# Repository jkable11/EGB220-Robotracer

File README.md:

# EGB220-Robotracer

FOR QUT EGB220 ROBOTRACER ASSIGNMENT SEM1 2016

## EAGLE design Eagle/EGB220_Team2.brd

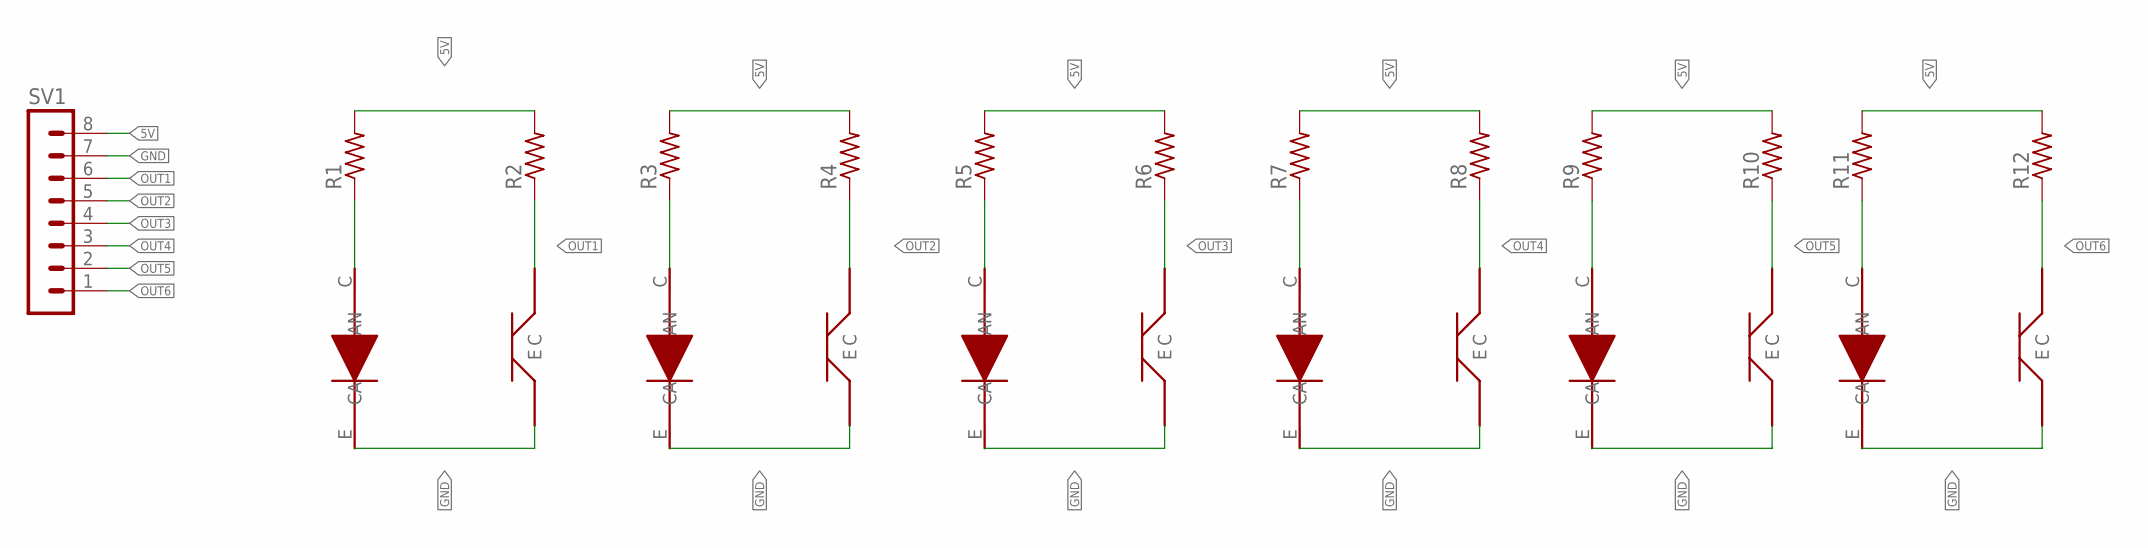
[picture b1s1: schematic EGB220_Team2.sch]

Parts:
LED-R1, LED-R3, LED-R5, LED-R7, LED-R9, LED-R11: LED; PHOTO-DIODE
R1, R2, R3, R4, R5, R6, R7, R8, R9, R10, R11, R12: R-US_0204/7; 0204/7
SV1: MA08-1
T-R2, T-R4, T-R6, T-R8, T-R10, T-R12: PHOTO_DIODE; PHOTO-DIODE

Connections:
5V: R1.2, R2.2, R3.2, R4.2, R5.2, R6.2, R7.2, R8.2, R9.2, R10.2, R11.2, R12.2, SV1.8
GND: LED-R1.E (CA), LED-R3.E (CA), LED-R5.E (CA), LED-R7.E (CA), LED-R9.E (CA), LED-R11.E (CA), SV1.7, T-R2.E, T-R4.E, T-R6.E, T-R8.E, T-R10.E, T-R12.E
unnamed: LED-R1.C (AN), R1.1
unnamed: LED-R3.C (AN), R3.1
unnamed: LED-R5.C (AN), R5.1
unnamed: LED-R7.C (AN), R7.1
unnamed: LED-R9.C (AN), R9.1
unnamed: LED-R11.C (AN), R11.1
OUT1: R2.1, SV1.6, T-R2.C
OUT2: R4.1, SV1.5, T-R4.C
OUT3: R6.1, SV1.4, T-R6.C
OUT4: R8.1, SV1.3, T-R8.C
OUT5: R10.1, SV1.2, T-R10.C
OUT6: R12.1, SV1.1, T-R12.C

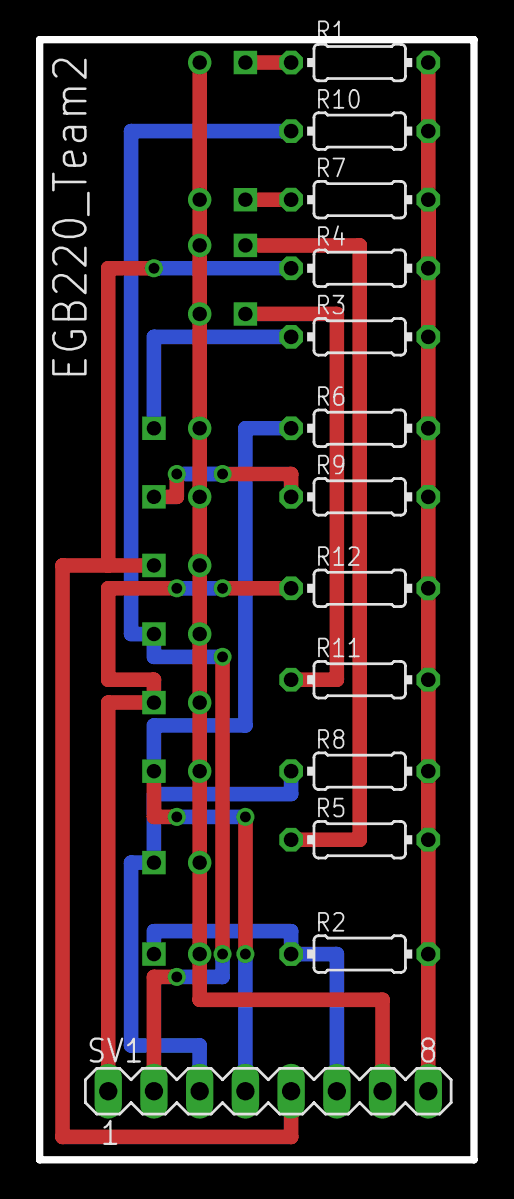
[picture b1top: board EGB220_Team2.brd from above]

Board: 2 copper layers, 24.1 x 62.2 mm, 25 parts (0 on the bottom side), 14 nets.

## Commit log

2016-03-18 :confetti_ball: Added .gitattributes & .gitignore files
2016-03-18 Setup project
2016-03-18 Added Eagle folder
    for pcb design stuff
2016-03-18 Added Burndown chart
    Dummy burndown chart need to fill in data
2016-03-19 Added some dummy data
    Added some dummy data and formatted graph properly
    also added approximate time i have been working on things so far (1 hr)
2016-03-19 Added matlab code to workout sprints left
    now has projected sprints left
2016-03-21 Added Jordan's makefile for the spark
2016-03-21 Changes to burndown chart data
    main changes by Jon, misc fixes by Alex
2016-03-21 Made program to make lights flash
    Wrote and tested basic bush button, makes one led flash
2016-03-23 Made .h file
2016-03-23 Designed PCB
    1.5 Hours
2016-03-23 Pooled hours
2016-04-01 PWM basics
    Just a copy and past from the computer lab
2016-04-01 Prevent compilation files from uploading
2016-04-06 Added sample code from tute
2016-04-07 light_sensor
    code to handle IR light sensor
    spent 4.5 hours to develop
